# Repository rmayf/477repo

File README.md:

477repo
=======

Hardware Capstone
CHANGE
CHANGE #2
this is a new lines

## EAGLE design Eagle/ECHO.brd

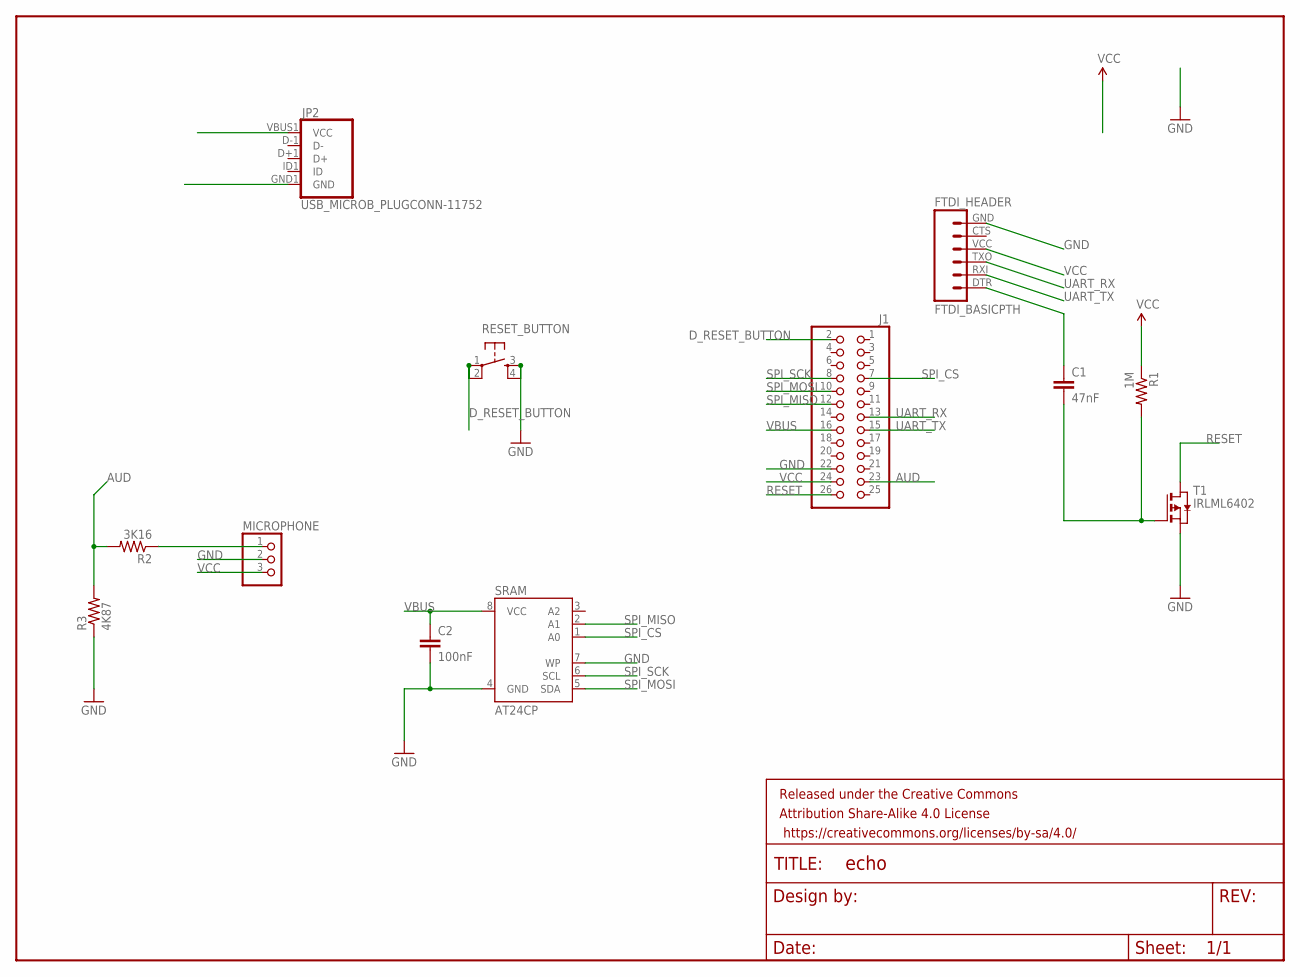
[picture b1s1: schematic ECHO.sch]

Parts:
C1: 47nF; 0603-CAP
C2: 100nF; 0603-CAP
FRAME1: FRAME-LETTER; CREATIVE_COMMONS
FTDI_HEADER: FTDI_BASICPTH; FTDI_BASIC
J1: PINHD-2X13; 2X13
JP2: USB_MICROB_PLUGCONN-11752; USB-B-MICRO-SMD_V03
MICROPHONE: PINHD-1X3; 1X03
R1: 1M; 0603-RES
R2: 3K16; 0603-RES
R3: 4K87; 0603-RES
RESET_BUTTON: TAC_SWITCHSMD; TACTILE-SWITCH-SMD
SRAM: AT24CP; DIL08
T1: IRLML6402; SOT-23

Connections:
AUD: J1.23, R2.2, R3.2
D_RESET_BUTTON: J1.2, RESET_BUTTON.1, RESET_BUTTON.2
GND: C2.2, FTDI_HEADER.GND (6), J1.22, JP2.GND1 (GND), MICROPHONE.2, R3.1, RESET_BUTTON.3, RESET_BUTTON.4, SRAM.4 (GND), SRAM.7 (WP), T1.2 (S)
unnamed: C1.1, FTDI_HEADER.DTR (1)
unnamed: C1.2, R1.2, T1.1 (G)
unnamed: MICROPHONE.1, R2.1
RESET: J1.26, T1.3 (D)
SPI_CS: J1.7, SRAM.1 (A0)
SPI_MISO: J1.12, SRAM.2 (A1)
SPI_MOSI: J1.10, SRAM.5 (SDA)
SPI_SCK: J1.8, SRAM.6 (SCL)
UART_RX: FTDI_HEADER.TXO (3), J1.13
UART_TX: FTDI_HEADER.RXI (2), J1.15
VBUS: C2.1, J1.16, JP2.VBUS1 (VCC), SRAM.8 (VCC)
VCC: FTDI_HEADER.VCC (4), J1.24, MICROPHONE.3, R1.1

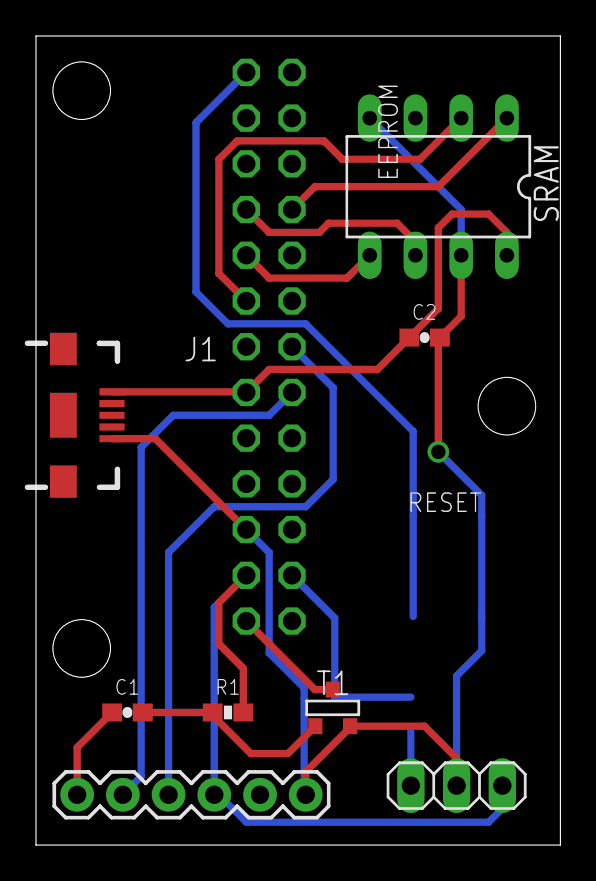
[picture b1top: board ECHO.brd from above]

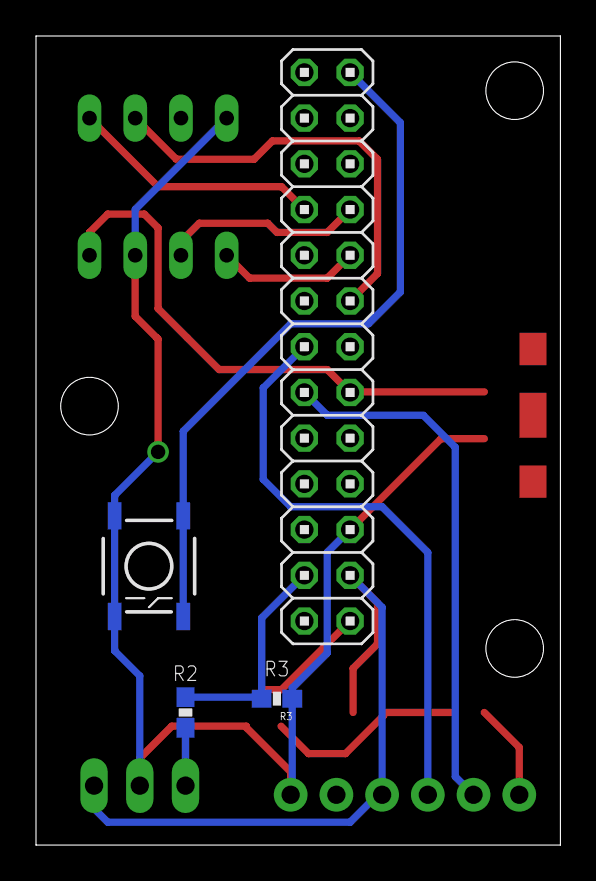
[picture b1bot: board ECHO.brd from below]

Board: 2 copper layers, 29.1 x 44.9 mm, 13 parts (4 on the bottom side), 15 nets.

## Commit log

2014-04-09 Jun's Test Commit
2014-04-09 Jun's Test Commit #2
2014-04-09 Jun's Test Commit #3
2014-04-11 Jun's 4th Test Commit
2014-04-11 Jun's 5th Test Commit
2014-04-11 Final Test
2014-04-18 add server .war file
2014-04-19 Add sample client/server code
2014-04-19 add README for android client/server
2014-04-19 edit README
2014-04-24 create android app branch:
2014-04-24 we have lift off
2014-04-24 cleaning
2014-04-24 Adding Aquila libraries and header
2014-04-25 done work
2014-04-27 changed the message header format a little
2014-04-27 cleaned
2014-04-27 testing
2014-04-27 setting up zee repo
2014-04-27 simple tester for upload
2014-04-27 upload now works and changed HTTP client to use https for parse
2014-04-27 created links to the xml files and put them in the src folder so they can be under version control
2014-04-29 mostly done, just need to know how to interface with the matlab process and Parse stuff
2014-04-29 added id to url
2014-04-29 solving all out problems
2014-04-29 added support for audfprint
2014-04-30 add android app sources
2014-04-30 add eclipse ADT project to source control
2014-04-30 remove redundant app/ directory
2014-05-01 update activites and app flows
2014-05-04 update app functionality
2014-05-05 commiting before I change it to include parse push stuff
2014-05-05 added permissions for parse push and it works now
2014-05-05 added the file that registers the device with Parse for pushes
2014-05-06 making progress towards subscribing to noises
2014-05-07 getting closer. added async fetch for the sound file
2014-05-07 made async task more robust. app doesnt crash if server is down
2014-05-07 implemented the methods to get and play event recordings and target recordings
2014-05-07 add custom views to settings/notifications lists
2014-05-09 first Parse and App UI integration
2014-05-09 integration v2
2014-05-09 integration v2.1 and gitignore update
2014-05-09 integration v2.2
2014-05-09 setting up code to pull audio samples
2014-05-09 integration v3
2014-05-09 about to merge
2014-05-10 implement add sample dialog UI functionality
2014-05-10 add delete dialog, fix configure button double click UI issue
2014-05-11 making progress
2014-05-11 adding a confirm delete fragment...doens't work yet but it doens't break it now either
2014-05-11 fuck the dialog to confirm delete for now. it just deletes it sorry
2014-05-11 taking a break for now...the components work its just not ideal
2014-05-13 flyport configuration with OPEN/WPA/WPA2 working
2014-05-13 got rid of a few unnecessary lines
2014-05-14 refactor code v1
2014-05-14 refactor v2
2014-05-14 refactor v2.1
2014-05-14 refactor v2.2
2014-05-18 Adding eagle schematics
2014-05-18 pushing code for mark to merge
2014-05-18 finished pcb layout
2014-05-18 no more queries for sound name
2014-05-19 reformat notifications and remove old files
2014-05-21 new logo
2014-05-22 added firmware
2014-05-30 adding sr measurment code
2014-05-30 Another file for another style
2014-05-30 SPI works
2014-06-01 update library (change types on some functions) and work on flyport code
2014-06-02 Fixed a bug with tcpclose funciton call
2014-06-02 made some minor changes
2014-06-03 taskFlyport, heard some audio
2014-06-04 moar progress
2014-06-05 minor UI updates
2014-06-05 added newline to end of file to kill compiler warnings
2014-06-05 adding the entire open picus ide project
2014-06-05 update activities to remove code from UI thread
2014-06-05 improve UI, refactor code, working on setup activity
2014-06-05 fixes to UI, before changes to setup activity
2014-06-05 pulling in marks changes
2014-06-07 improve setup flow and user experience
2014-06-07 fix app crash on push receive if notifications window has never been opened
2014-06-07 before revamp of envelope
2014-06-07 improved peak finder
2014-06-08 removing project.properties from index
2014-06-08 gonna change the async task for http requests to klement a little bit
2014-06-08 refactor sample playing code and add UI for notification delete
2014-06-08 implemented the stuff that doesn't work in cloud code in android
2014-06-08 minor updates
2014-06-08 update Settings/Notification Activities
2014-06-08 goiong to pull in marks changes
2014-06-08 notification deletion works. haven't tested it thoroughly but its pretty much the same code as deletion of match targets
2014-06-08 removed the double call to the async task
2014-06-08 fix setup error string
2014-06-08 freq detection is better now
2014-06-08 fixes
2014-06-09 UI changes for better user experience
2014-06-09 UI improvements, improve wording of some prompts
2014-06-09 fixed null pointer

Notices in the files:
parts and their libraries:
SparkFun-Aesthetics: Licensing: Creative Commons ShareAlike 4.0 International - https://creativecommons.org/licenses/by-sa/4.0
SparkFun-Aesthetics: Released under the Creative Commons Attribution Share-Alike 4.0 License
SparkFun-Aesthetics: https://creativecommons.org/licenses/by-sa/4.0
